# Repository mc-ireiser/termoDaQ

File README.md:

# termoDaQ

termoDaQ is a development board based on the [Arduino](https://www.arduino.cc/) architecture, uses an [ATmega328-P](http://ww1.microchip.com/downloads/en/DeviceDoc/Atmel-42735-8-bit-AVR-Microcontroller-ATmega328-328P_Summary.pdf) and an [ATtiny85](http://ww1.microchip.com/downloads/en/DeviceDoc/Atmel-2586-AVR-8-bit-Microcontroller-ATtiny25-ATtiny45-ATtiny85_Datasheet-Summary.pdf) for its operation.

This board was originally designed to help the work of oceanography students, serving as an instrument for the acquisition of physical variables (temperature, pressure) at surface level in bodies of fresh water, in order to detect changes that may affect the flora or fauna of ecosystems, automating the work of making measurements over time.

But it can serve many purposes since it has a connection for GPS receivers, pressure sensor, multiple temperature sensors (internal and external), two additional inputs for any analog sensor (such as rain, flow or UV) and SD card.

The function of the [ATtiny85](http://ww1.microchip.com/downloads/en/DeviceDoc/Atmel-2586-AVR-8-bit-Microcontroller-ATtiny25-ATtiny45-ATtiny85_Datasheet-Summary.pdf) is work as a timer to program the operation cycles of the equipment, reducing the energy consumption, which allows incrementing the operation time when the battery is used. To achieve this, activate and deactivate the sensors area.

The function of the [ATmega328-P](http://ww1.microchip.com/downloads/en/DeviceDoc/Atmel-42735-8-bit-AVR-Microcontroller-ATmega328-328P_Summary.pdf) is to control the sensors area, managing each of them to perform the measurement and data storage processes.

## Operation

The board is divided into three parts

1) Power supply.
2) Energy management.
3) Sensors area.

In particular, I'm responsible for developing the energy management and the sensors area.

For the energy management, is used the [ATtiny85](http://ww1.microchip.com/downloads/en/DeviceDoc/Atmel-2586-AVR-8-bit-Microcontroller-ATtiny25-ATtiny45-ATtiny85_Datasheet-Summary.pdf) microcontroller to carry out cycles that enable or disable the sensors, cutting off the power in periods where no measurements are needed.

As for the sensors area, its function is to perform the measurements and store the data. Only one cycle at a time, at the end one signal is sent to the energy management area to cut the power.

## Pinout

## Board specifications

All the source files are in this repository

- Board Size: 99.82 mm X 73.41 mm (X = 99.82, Y = 73.41)
- Number of layers: 2
- Number of drills: 311
- Number of vias: 47
- Number of signals: 146
- Minimum copper trace width: 0.41 mm
- Consumption: ~ 80mAh (currently under test)

### ATtiny85

|Name | Value |
| ---------- | ---------- |
|Operating Voltage Range (V) | 1.8 to 5.5 |
|Temperature Range (C) | -40 to 85 |
|CPU Speed (MIPS/DMIPS) | 20 |
|Pin Count | 8 |
|Program Memory Type | Flash |
|Program Memory Size (KB) | 8 |
|SRAM Bytes | 512 |
|Data EEPROM/HEF (bytes) | 512 |
|Digital Communication Peripherals | 1-SPI, 1-I2C |
|Capture/Compare/PWM Peripherals | 5PWM |
|Timers | 2 x 8-bit |
|Number of Comparators | 1 |

### ATmega328P

| Name | Value |
| ---------- | ---------- |
|Operating Supply Voltage | 1.8 V to 5.5 V |
|Temperature Range (C) | - 40 to 85 |
|Maximum Clock Frequency | 20 MHz |
|Pin count | 28 |
|Number of I/Os | 23 I/O |
|Program Memory Type | Flash |
|Program Memory Size | 32 kB |
|Data Bus Width | 8 bit |
|Data RAM Type | SRAM |
|Data RAM Size | 2 kB |
|Data ROM Type | EEPROM |
|Data ROM Size | 1 kB |
|Number of ADC Channels | 6 |
|ADC Resolution | 10 bit |
|Interface Type | I2C, SPI, USART |
|Number of Timers/Counters | 3 Timer |

## Translation

English translation using google translator.

If you wish, you can help me translate the readme file correctly.

## License

Creative Commons Attribution-ShareAlike 4.0 International Public License

Please go to the License section for more information. [Link](https://github.com/mc-ireiser/termoDaQ/tree/master/License)

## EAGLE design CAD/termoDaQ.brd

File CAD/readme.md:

# Description of files

- .brd source file with the design of the PCB
- .sch source file with the schematics of the board

These files are licensed under: Creative Commons Attribution-ShareAlike 4.0 International Public License

## Schematics

## Disclaimer

Last updated: October 05, 2018

(the "Service", files contained on this page)

Jesus Rodriguez assumes no responsibility for errors or omissions in the contents on the Service.

In no event shall Jesus Rodriguez be liable for any special, direct, indirect, consequential, or incidental damages or any damages whatsoever, whether in an action of contract, negligence or other tort, arising out of or in connection with the use of the Service or the contents of the Service. Jesus Rodriguez reserves the right to make additions, deletions, or modification to the contents on the Service at any time without prior notice.

This Disclaimer for Jesus Rodriguez is managed by TermsFeed Disclaimer Generator

Jesus Rodriguez does not warrant that the website is free of viruses or other harmful components.

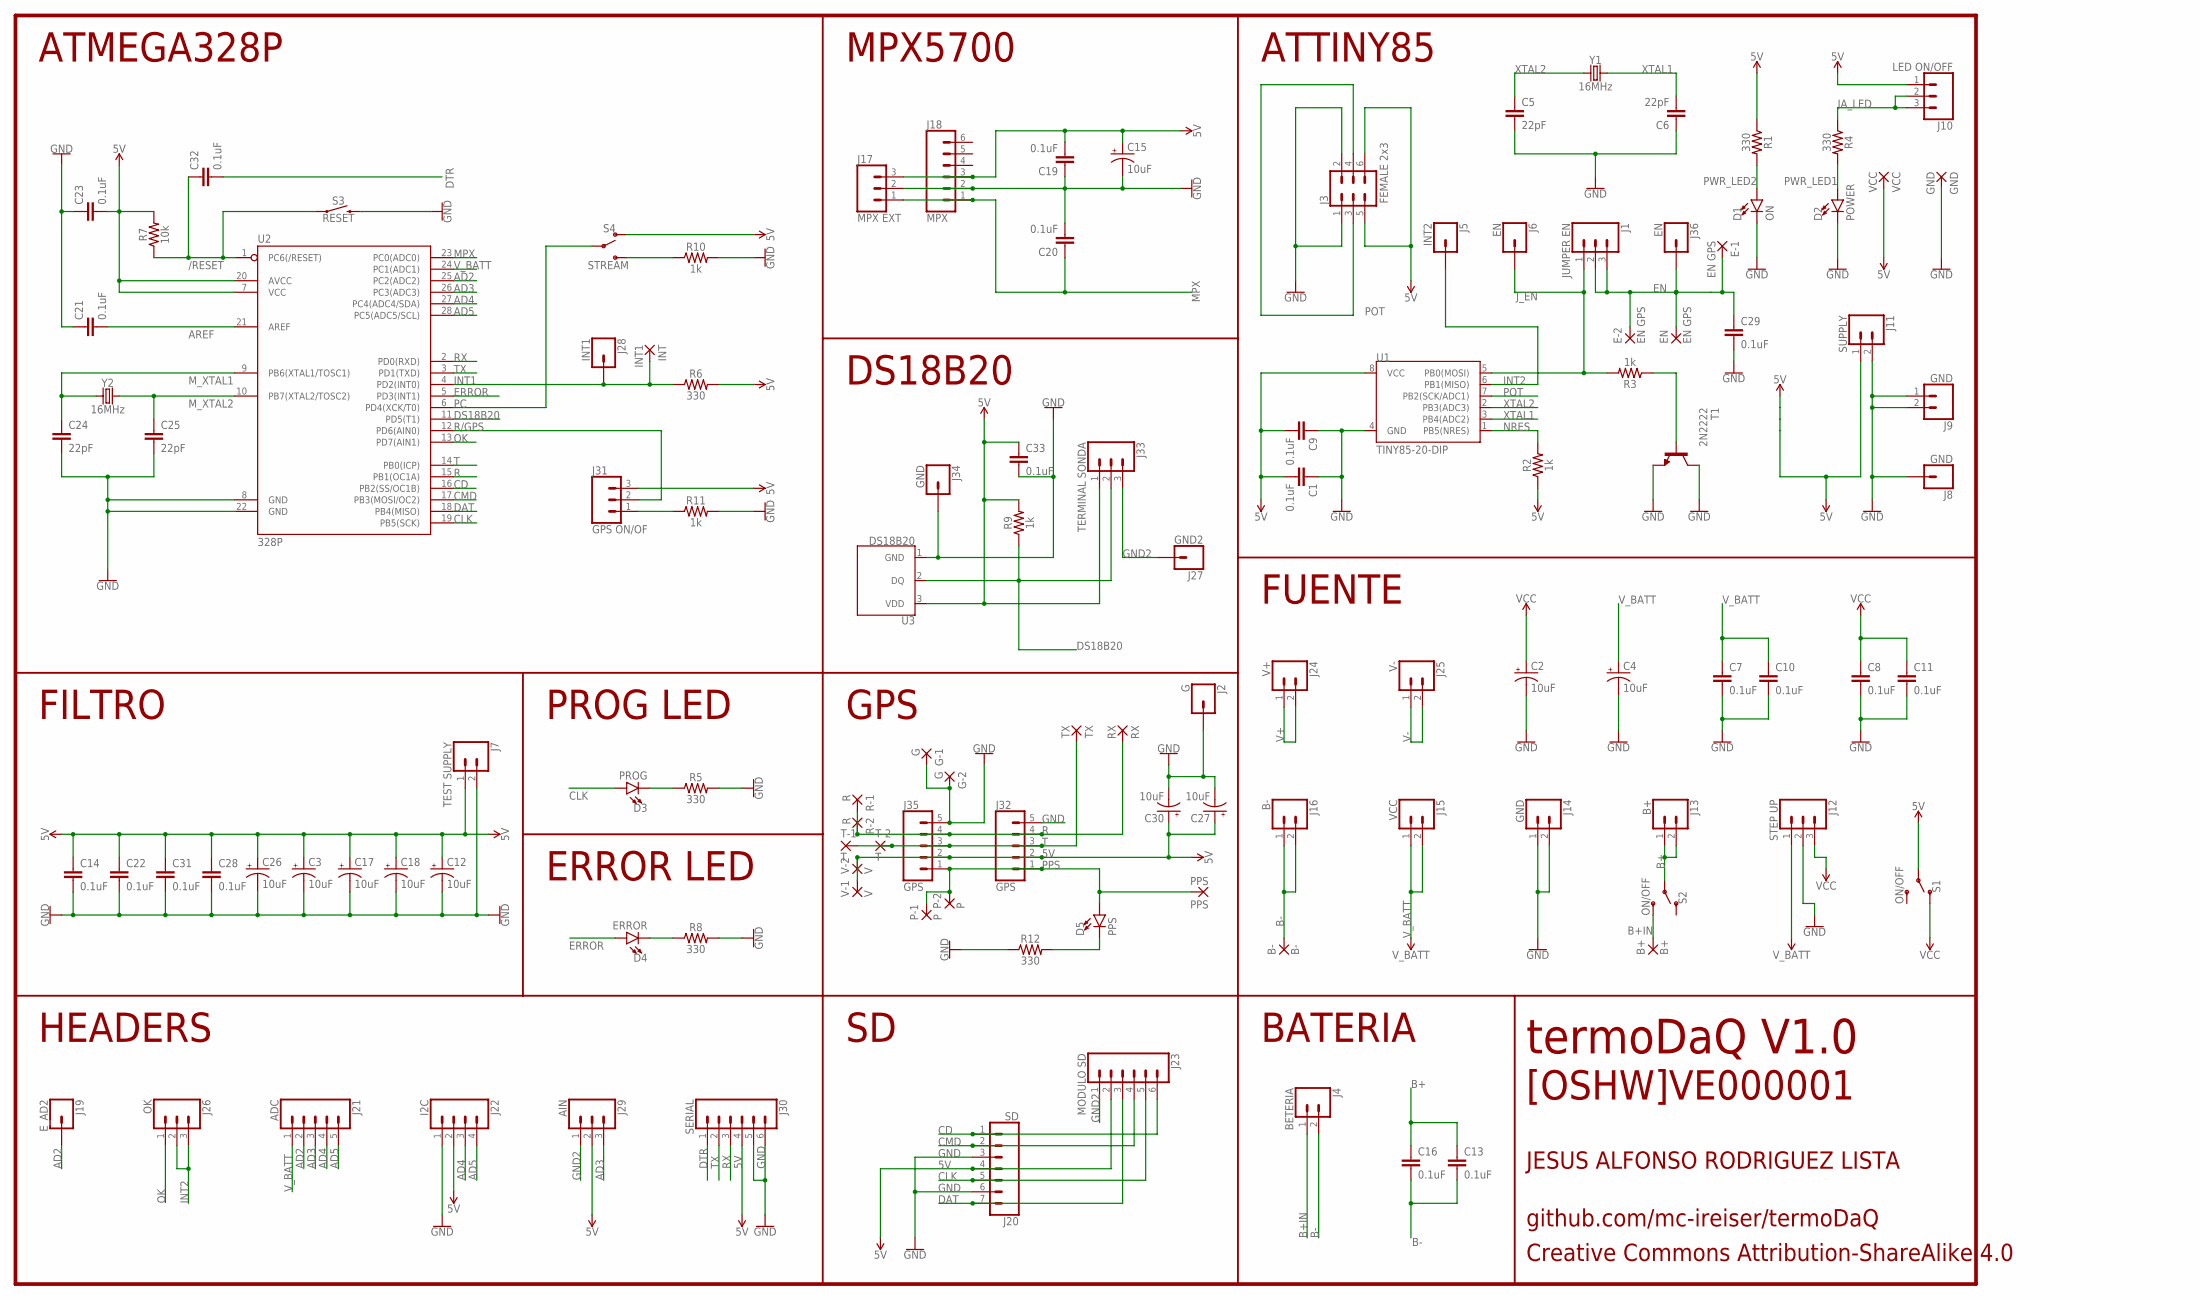
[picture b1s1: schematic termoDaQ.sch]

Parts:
B+: B+; SMD2,54-5,08
B-: B-; SMD2,54-5,08
C1, C7, C8, C9, C10, C11, C13, C14, C16, C19, C20, C21, C22, C23, C28, C29, C31, C32, C33: 0.1uF; CAP-PTH-SMALL-KIT
C2, C3, C4, C12, C15, C17, C18, C26, C27, C30: 10uF; CPOL-RADIAL-2.5MM-5MM
C5, C6, C24, C25: 22pF; CAP-PTH-2.54
D1: ON; LED_5MM
D2: POWER; LED_3MM
D3: PROG; LED_5MM
D4: ERROR; LED_5MM
D5: PPS; LED_5MM
E-1, E-2: EN GPS; SMD1,27-2,54
EN: EN GPS; SMD1,27-2,54
G-1, G-2: G; SMD1,27-2,54
GND: GND; SMD1,27-2,54
INT: INT1; SMD1,27-2,54
J1: JUMPER EN; 1X03
J2: G; 1X01
J3: FEMALE 2x3; 2X3
J4: BETERIA; 1X02
J5: INT2; 1X01
J6, J36: EN; 1X01
J7: TEST SUPPLY; 1X02
J8, J34: GND; 1X01
J9, J14: GND; 1X02
J10: LED ON/OFF; 1X03
J11: SUPPLY; 1X02
J12: STEP UP; 1X03
J13: B+; 1X02
J15: VCC; 1X02
J16: B-; 1X02
J17: MPX EXT; 1X03
J18: MPX; 1X06
J19: E_AD2; 1X01
J20: SD; 1X07
J21: ADC; 1X05
J22: I2C; 1X04
J23: MODULO SD; MOLEX-1X6
J24: V+; 1X02
J25: V-; 1X02
J26: OK; 1X03
J27: GND2; 1X01
J28: INT1; 1X01
J29: AIN; 1X03
J30: SERIAL; 1X06
J31: GPS ON/OF; 1X03
J32, J35: GPS; 1X05
J33: TERMINAL SONDA; SCREWTERMINAL-5MM-3
P-1, P-2: P; SMD1,27-2,54
PPS: PPS; SMD1,27-2,54
R1, R4, R5, R6, R8, R12: 330; AXIAL-0.3
R2, R3, R9, R10, R11: 1k; AXIAL-0.3
R7: 10k; AXIAL-0.3
R-1, R-2: R; SMD1,27-2,54
RX: RX; SMD1,27-2,54
S1, S2: ON/OFF; SWITCH_SPDT_PTH_11.6X4.0MM
S3: RESET; TACTILE_SWITCH_PTH_6.0MM
S4: STREAM; SWITCH_SPDT_PTH_11.6X4.0MM
T1: 2N2222; TO92-EBC-OVAL
T-1, T-2: T; SMD1,27-2,54
TX: TX; SMD1,27-2,54
U1: TINY85-20-DIP; DIP08_MCU
U2: 328P; DIP28
U3: DS18B20; TO-92-AMMO
V-1, V-2: V; SMD1,27-2,54
VCC: VCC; SMD1,27-2,54
Y1, Y2: 16MHz; HC49US

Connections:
5V: C1.2, C3.1 (+), C9.2, C12.1 (+), C14.1, C15.1 (+), C17.1 (+), C18.1 (+), C19.2, C22.1, C23.2, C26.1 (+), C27.1 (+), C28.1, C30.1 (+), C31.1, C33.1, J3.5, J3.6, J7.1, J10.1, J11.1, J17.3, J18.3, J20.4, J22.2, J23.2, J29.2, J30.4, J31.3, J32.2, J33.1, J35.2, R1.P$1 (1), R2.P$1 (1), R6.P$2 (2), R7.P$2 (2), R9.P$2 (2), S1.2, S4.1 (O), U1.8 (VCC), U2.7 (VCC), U2.20 (AVCC), U3.3 (VDD), V-1.1, V-2.1, VCC.1
/RESET: C32.1, R7.P$1 (1), S3.1, U2.1 (PC6(/RESET))
AD2: J19.1, J21.2, U2.25 (PC2(ADC2))
AD3: J21.3, J29.3, U2.26 (PC3(ADC3))
AD4: J21.4, J22.3, U2.27 (PC4(ADC4/SDA))
AD5: J21.5, J22.4, U2.28 (PC5(ADC5/SCL))
AREF: C21.2, U2.21 (AREF)
B+: C13.1, C16.1, J13.1, J13.2, S2.2
B+IN: B+.1, J4.1, S2.3 (S)
B-: B-.1, C13.2, C16.2, J4.2, J16.1, J16.2
CD: J20.1, J23.6, U2.16 (PB2(SS/OC1B))
CLK: D3.A, J20.5, J23.5, U2.19 (PB5(SCK))
CMD: J20.2, J23.4, U2.17 (PB3(MOSI/OC2))
DAT: J20.7, J23.3, U2.18 (PB4(MISO))
DS18B20: J33.2, R9.P$1 (1), U2.11 (PD5(T1)), U3.2 (DQ)
DTR: C32.2, J30.1
EN: C29.1, E-1.1, E-2.1, EN.1, J1.2, J1.3, J36.1
ERROR: D4.A, U2.5 (PD3(INT1))
GND: C1.1, C2.2 (-), C3.2 (-), C4.2 (-), C5.2, C6.1, C7.2, C8.2, C9.1, C10.2, C11.2, C12.2 (-), C14.2, C15.2 (-), C17.2 (-), C18.2 (-), C19.1, C20.2, C21.1, C22.2, C23.1, C24.2, C25.2, C26.2 (-), C27.2 (-), C28.2, C29.2, C30.2 (-), C31.2, C33.2, D1.K (C), D2.K (C), G-1.1, G-2.1, GND.1, J2.1, J3.1, J3.2, J7.2, J8.1, J9.1, J9.2, J11.2, J12.2, J14.1, J14.2, J17.2, J18.2, J20.3, J20.6, J22.1, J30.5, J30.6, J32.5, J34.1, J35.5, R5.P$2 (2), R8.P$2 (2), R10.P$2 (2), R11.P$2 (2), R12.P$1 (1), S3.3 (2), T1.C, T1.E, U1.4 (GND), U2.8 (GND), U2.22 (GND), U3.1 (GND)
GND2: J23.1, J27.1, J29.1, J33.3
INT1: INT.1, J28.1, R6.P$1 (1), U2.4 (PD2(INT0))
INT2: J5.1, J26.2, J26.3, U1.6 (PB1(MISO))
JA_LED: J10.2, J10.3, R4.P$1 (1)
J_EN: J1.1, J6.1, R3.P$2 (2), U1.5 (PB0(MOSI))
MPX: C20.1, J17.1, J18.1, U2.23 (PC0(ADC0))
M_XTAL1: C24.1, U2.9 (PB6(XTAL1/TOSC1)), Y2.1
M_XTAL2: C25.1, U2.10 (PB7(XTAL2/TOSC2)), Y2.2
unnamed: D3.K (C), R5.P$1 (1)
unnamed: D5.K (C), R12.P$2 (2)
unnamed: D4.K (C), R8.P$1 (1)
unnamed: J31.1, R11.P$1 (1)
unnamed: R10.P$1 (1), S4.3 (S)
unnamed: R3.P$1 (1), T1.B
NRES: R2.P$2 (2), U1.1 (PB5(NRES))
OK: J26.1, U2.13 (PD7(AIN1))
PC: S4.2, U2.6 (PD4(XCK/T0))
POT: J3.3, J3.4, U1.7 (PB2(SCK/ADC1))
PPS: D5.A, J32.1, J35.1, P-1.1, P-2.1, PPS.1
PWR_LED1: D2.A, R4.P$2 (2)
PWR_LED2: D1.A, R1.P$2 (2)
R: J32.4, J35.4, R-1.1, R-2.1, RX.1, U2.15 (PB1(OC1A))
R/GPS: J31.2, U2.12 (PD6(AIN0))
RX: J30.3, U2.2 (PD0(RXD))
T: J32.3, J35.3, T-1.1, T-2.1, TX.1, U2.14 (PB0(ICP))
TX: J30.2, U2.3 (PD1(TXD))
V+: J24.1, J24.2
V-: J25.1, J25.2
VCC: C2.1 (+), C8.1, C11.1, J12.3, S1.1 (O)
V_BATT: C4.1 (+), C7.1, C10.1, J12.1, J15.1, J15.2, J21.1, U2.24 (PC1(ADC1))
XTAL1: C6.2, U1.3 (PB4(ADC2)), Y1.2
XTAL2: C5.1, U1.2 (PB3(ADC3)), Y1.1

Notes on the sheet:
FUENTE
ATTINY85
ATMEGA328P
HEADERS
JESUS ALFONSO RODRIGUEZ LISTA
GPS
DS18B20
MPX5700
PROG LED
FILTRO
ERROR LED
BATERIA
[OSHW]VE000001
github.com/mc-ireiser/termoDaQ
Creative Commons Attribution-ShareAlike 4.0
termoDaQ V1.0

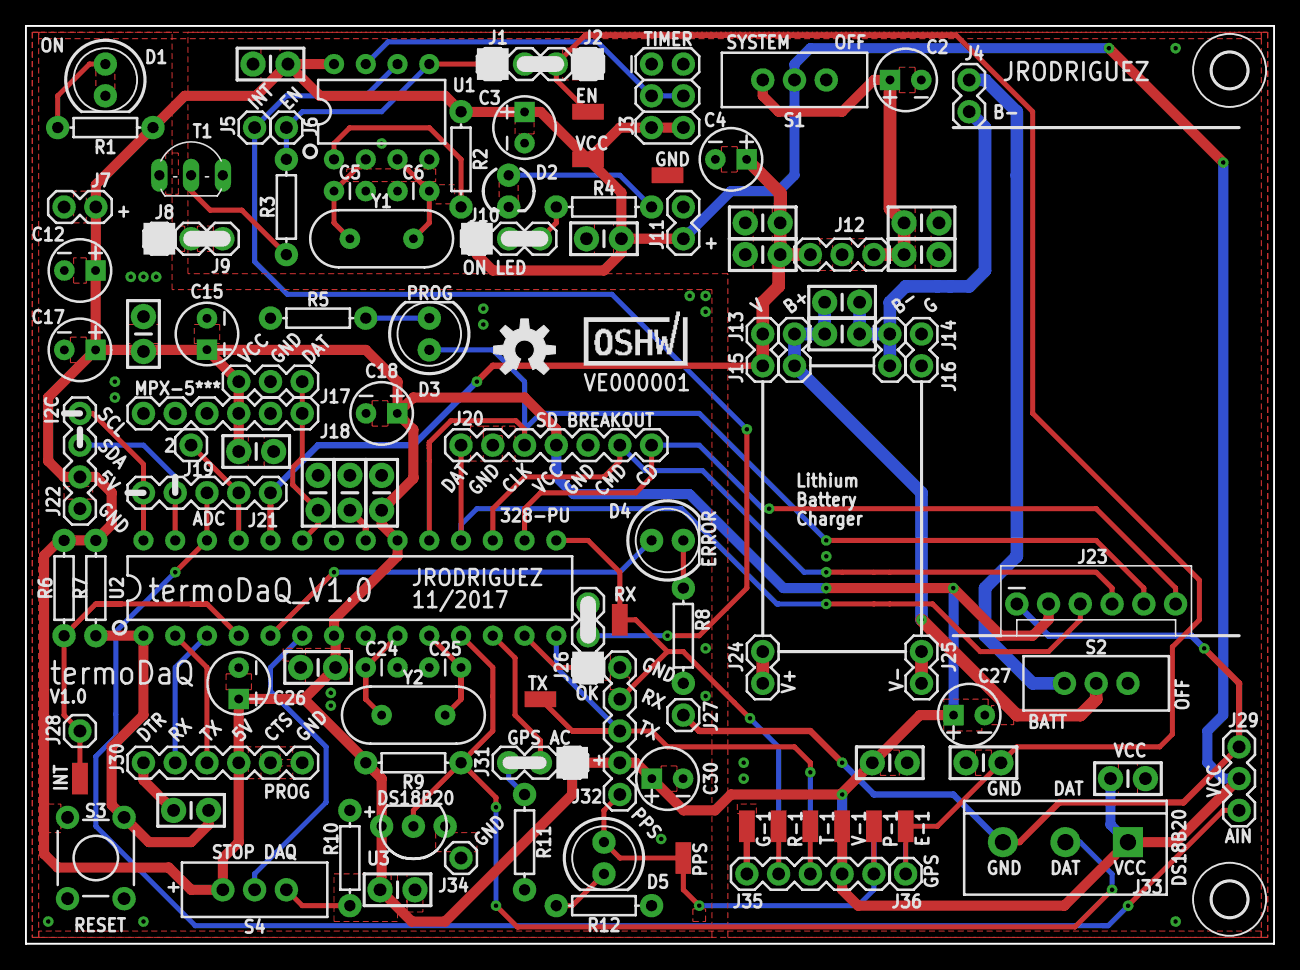
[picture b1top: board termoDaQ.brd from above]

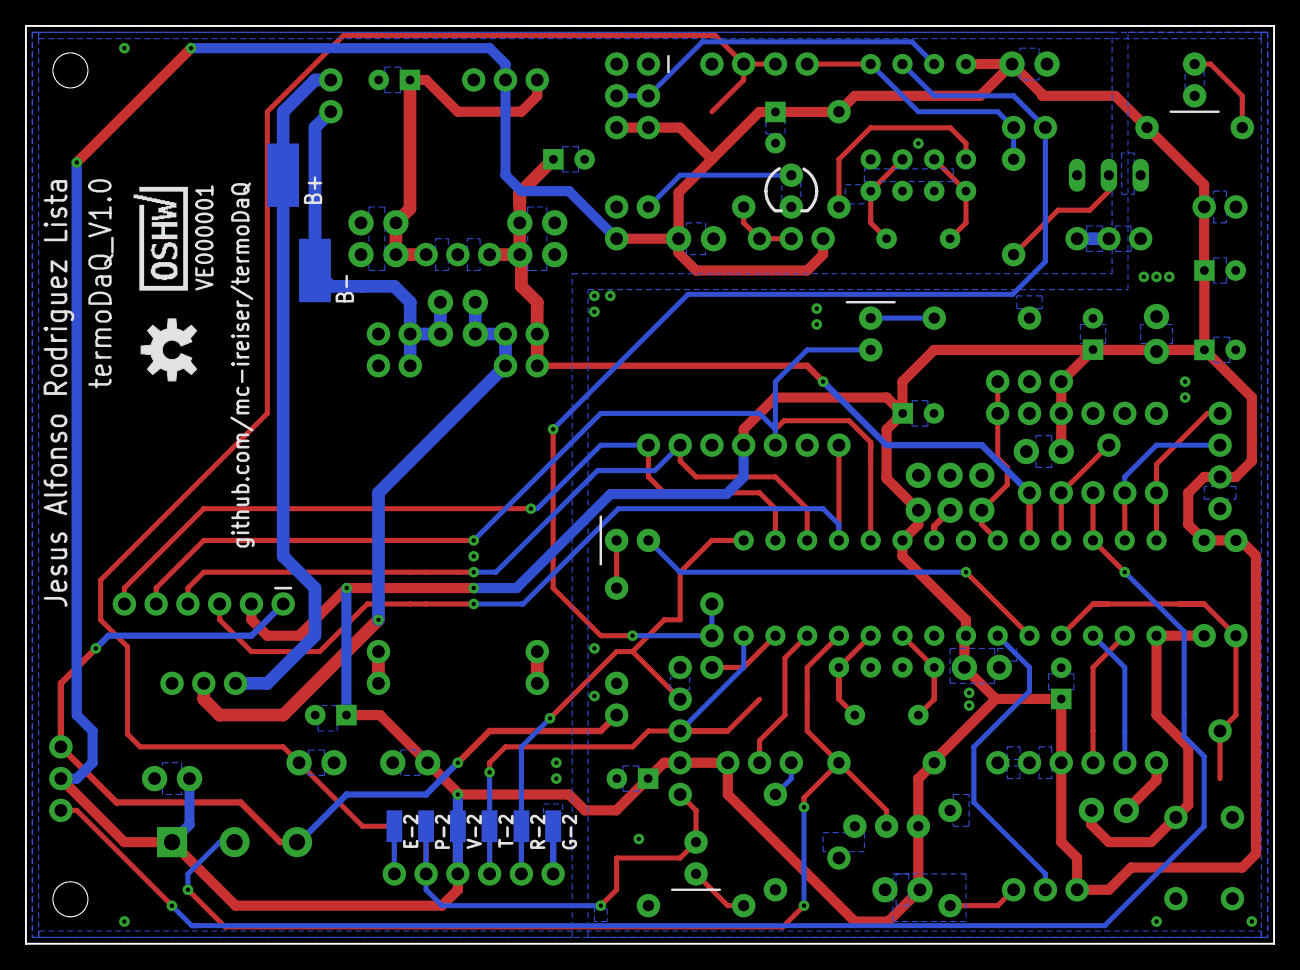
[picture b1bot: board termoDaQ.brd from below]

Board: 2 copper layers, 99.8 x 73.4 mm, 123 parts (10 on the bottom side), 51 nets.

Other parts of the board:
U$1, U$100: OSHW-LOGO-M
U$2, U$101: CERT-SMALL-SILK
U$3, U$4: 2,8

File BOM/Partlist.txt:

Partlist

Exported from termoDaQ.brd

EAGLE Version 9.1.3 Copyright (c) 1988-2018 Autodesk, Inc.

Assembly variant: 

Part     Value          Package                    Library                     Position (inch)       Orientation

C1       0.1uF          CAP-PTH-SMALL-KIT          SparkFun-Capacitors         (0.8 2.8)             R0
C2       10uF           CPOL-RADIAL-2.5MM-5MM      SparkFun-Capacitors         (2.8 2.75)            R180
C3       10uF           CPOL-RADIAL-2.5MM-5MM      SparkFun-Capacitors         (1.6 2.6)             R90
C4       10uF           CPOL-RADIAL-2.5MM-5MM      SparkFun-Capacitors         (2.25 2.5)            R0
C5       22pF           CAP-PTH-2.54               SparkFun-Capacitors         (1.05 2.4)            R0
C6       22pF           CAP-PTH-2.54               SparkFun-Capacitors         (1.25 2.4)            R0
C7       0.1uF          CAP-PTH-SMALL-KIT          SparkFun-Capacitors         (2.35 2.3)            R180
C8       0.1uF          CAP-PTH-SMALL-KIT          SparkFun-Capacitors         (2.85 2.3)            R0
C9       0.1uF          CAP-PTH-SMALL-KIT          SparkFun-Capacitors         (1.85 2.25)           R0
C10      0.1uF          CAP-PTH-SMALL-KIT          SparkFun-Capacitors         (2.35 2.2)            R180
C11      0.1uF          CAP-PTH-SMALL-KIT          SparkFun-Capacitors         (2.85 2.2)            R0
C12      10uF           CPOL-RADIAL-2.5MM-5MM      SparkFun-Capacitors         (0.2 2.15)            R0
C13      0.1uF          CAP-PTH-SMALL-KIT          SparkFun-Capacitors         (2.6 2.05)            R0
C14      0.1uF          CAP-PTH-SMALL-KIT          SparkFun-Capacitors         (0.4 1.95)            R90
C15      10uF           CPOL-RADIAL-2.5MM-5MM      SparkFun-Capacitors         (0.6 1.95)            R270
C16      0.1uF          CAP-PTH-SMALL-KIT          SparkFun-Capacitors         (2.6 1.95)            R0
C17      10uF           CPOL-RADIAL-2.5MM-5MM      SparkFun-Capacitors         (0.2 1.9)             R0
C18      10uF           CPOL-RADIAL-2.5MM-5MM      SparkFun-Capacitors         (1.15 1.7)            R0
C19      0.1uF          CAP-PTH-SMALL-KIT          SparkFun-Capacitors         (0.755 1.58)          R180
C20      0.1uF          CAP-PTH-SMALL-KIT          SparkFun-Capacitors         (0.95 1.45)           R90
C21      0.1uF          CAP-PTH-SMALL-KIT          SparkFun-Capacitors         (1.05 1.45)           R270
C22      0.1uF          CAP-PTH-SMALL-KIT          SparkFun-Capacitors         (1.15 1.45)           R90
C23      0.1uF          CAP-PTH-SMALL-KIT          SparkFun-Capacitors         (0.95 0.9)            R0
C24      22pF           CAP-PTH-2.54               SparkFun-Capacitors         (1.15 0.9)            R0
C25      22pF           CAP-PTH-2.54               SparkFun-Capacitors         (1.35 0.9)            R180
C26      10uF           CPOL-RADIAL-2.5MM-5MM      SparkFun-Capacitors         (0.7 0.85)            R270
C27      10uF           CPOL-RADIAL-2.5MM-5MM      SparkFun-Capacitors         (3 0.75)              R180
C28      0.1uF          CAP-PTH-SMALL-KIT          SparkFun-Capacitors         (2.75 0.6)            R0
C29      0.1uF          CAP-PTH-SMALL-KIT          SparkFun-Capacitors         (3.045 0.6)           R180
C30      10uF           CPOL-RADIAL-2.5MM-5MM      SparkFun-Capacitors         (2.05 0.55)           R180
C31      0.1uF          CAP-PTH-SMALL-KIT          SparkFun-Capacitors         (3.5 0.55)            R0
C32      0.1uF          CAP-PTH-SMALL-KIT          SparkFun-Capacitors         (0.55 0.45)           R180
C33      0.1uF          CAP-PTH-SMALL-KIT          SparkFun-Capacitors         (1.2 0.2)             R0
D1       ON             LED_5MM                    SparkFun-LED                (0.28 2.75)           R270
D2       POWER          LED_3MM                    SparkFun-LED                (1.55 2.4)            R270
D3       PROG           LED_5MM                    SparkFun-LED                (1.3 1.95)            R90
D4       ERROR          LED_5MM                    SparkFun-LED                (2.05 1.3)            R0
D5       PPS            LED_5MM                    SparkFun-LED                (1.85 0.3)            R270
J1       JUMPER EN      1X03                       SparkFun-Connectors         (1.5 2.8)             R0
J4       BETERIA        1X02                       SparkFun-Connectors         (3 2.75)              R270
J7       TEST SUPPLY    1X02                       SparkFun-Connectors         (0.25 2.35)           R180
J10      LED ON/OFF     1X03                       SparkFun-Connectors         (1.45 2.25)           R0
J11      SUPPLY         1X02                       SparkFun-Connectors         (2.1 2.25)            R90
J22      I2C            1X04                       SparkFun-Connectors         (0.2 1.4)             R90
J26      OK             1X03                       SparkFun-Connectors         (1.8 0.9)             R90
J30      SERIAL         1X06                       SparkFun-Connectors         (0.4 0.6)             R0
J31      GPS ON/OF      1X03                       SparkFun-Connectors         (1.55 0.6)            R0
J33      TERMINAL SONDA SCREWTERMINAL-5MM-3        SparkFun-Connectors         (3.5 0.35)            R180
R1       330            AXIAL-0.3                  SparkFun-Resistors          (0.28 2.6)            R180
R2       1k             AXIAL-0.3                  SparkFun-Resistors          (1.4 2.5)             R270
R3       1k             AXIAL-0.3                  SparkFun-Resistors          (0.85 2.35)           R90
R4       330            AXIAL-0.3                  SparkFun-Resistors          (1.85 2.35)           R0
R5       330            AXIAL-0.3                  SparkFun-Resistors          (0.95 2)              R180
R6       330            AXIAL-0.3                  SparkFun-Resistors          (0.15 1.15)           R90
R7       10k            AXIAL-0.3                  SparkFun-Resistors          (0.25 1.15)           R90
R8       330            AXIAL-0.3                  SparkFun-Resistors          (2.1 1)               R270
R9       1k             AXIAL-0.3                  SparkFun-Resistors          (1.25 0.6)            R180
R10      1k             AXIAL-0.3                  SparkFun-Resistors          (1.05 0.3)            R90
R11      1k             AXIAL-0.3                  SparkFun-Resistors          (1.6 0.35)            R270
R12      330            AXIAL-0.3                  SparkFun-Resistors          (1.85 0.15)           R180
S1       ON/OFF         SWITCH_SPDT_PTH_11.6X4.0MM SparkFun-Switches           (2.45 2.75)           R90
S2       ON/OFF         SWITCH_SPDT_PTH_11.6X4.0MM SparkFun-Switches           (3.4 0.85)            R270
S3       RESET          TACTILE_SWITCH_PTH_6.0MM   SparkFun-Switches           (0.25 0.3)            R270
S4       STREAM         SWITCH_SPDT_PTH_11.6X4.0MM SparkFun-Switches           (0.75 0.2)            R90
T1       2N2222         TO92-EBC-OVAL              adafruit                    (0.55 2.5)            R0
TX       TX             SMD1,27-2,54               wirepad                     (1.65 0.8)            R270
U1       TINY85-20-DIP  DIP08_MCU                  SparkFun-Retired            (1.15 2.65)           R0
U2       328P           DIP28                      SparkFun-IC-Microcontroller (1.05 1.15)           R0
U3       DS18B20        TO-92-AMMO                 SparkFun-Sensors            (1.25 0.4)            R180
Y1       16MHz          HC49US                     SparkFun-Clocks             (1.15 2.25)           R0
Y2       16MHz          HC49US                     SparkFun-Clocks             (1.25 0.75)           R0

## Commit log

2017-11-21 2D Render images files
2017-11-21 3D Render images files
2017-11-21 Bom and Partlist
2017-11-21 Source files .brd and .sch from Eagle 8.4
2017-11-21 Gerbers files for FAB
2017-11-21 images of Overall an Copper
2017-11-21 Libraries Adafruit and SparkFun - source link and .zip
2017-11-21 Licence info
2017-11-21 PDF files of board and Schematics
2017-11-21 STL model, only for demo!
2017-11-21 Firmware Attention
2017-11-21 Proroboard Assembly full test
2017-11-21 License repo link
2017-11-21 Link to test assembly img
2017-11-21 Link of license files
2017-11-21 include images
2017-11-21 License logo
2017-11-21 License update
2017-11-21 update title
2017-11-21 Set theme jekyll-theme-cayman
2017-11-21 aclaration
2017-11-21 docs folder add
2017-11-22 Create CNAME
2017-11-23 Update CNAME
2017-11-23 Example mockup
2017-11-23 Update mockup
2017-11-23 Updated mockup
2017-11-23 Delete
2017-11-23 Creative commons img
2017-11-23 Set theme jekyll-theme-leap-day
2017-11-23 Readme for preview
2017-11-23 Correction
2017-11-23 Description of files
2017-11-23 Pinout
2017-11-23 No copper preview
2017-11-24 updated with pinout
2017-11-25 Readme update
2017-11-25 Source files update
2017-11-25 New STL model
2017-11-25 Partlist update
2017-11-25 Expand Pinout IMG
2017-11-25 Re-Upload images files
2017-11-25 Re-Upload PDF files
2017-11-25 BOM on ods format
2017-11-25 Repair header
2017-11-25 Add 2D render
2017-11-25 Add Pending
2017-11-26 Fix 2D Render header
2017-11-26 Important update, start the manufacturing process in PCB
2017-11-26 add .
2018-01-19 Gerbers update
2018-01-19 Delay
2018-01-19 Info update!
2018-01-19 Photographs of the assembled board
2018-01-19 PCB assembled
2018-01-19 Update from main README
2018-01-19 img order
2018-01-20 STL model
2018-09-07 README
2018-09-07 Pendings list
2018-09-07 Old Update
2018-10-05 New 2D render
2018-10-05 Update, part list
2018-10-05 Source files, Update
2018-10-05 Prev img
2018-10-05 Updated, Gerbers files
2018-10-05 Updated, PDF schematics
2018-10-05 Update, Readme
2018-10-05 Link to new OSHWA page
2018-10-05 Disclaimer
2018-10-05 Update, Img
2018-10-05 Update, photographs
2018-10-05 3D render "old"
    Update required
2018-10-05 Fix format img
2018-10-05 Header img
2018-10-05 New schema
2018-10-05 Update, info
2018-10-05 Update, docs Readme
2018-10-05 Update, Disclaimer
2018-10-05 Update, Intro
2018-10-05 Update, Board specifications
2018-10-05 Fix table error
2018-10-05 Update, Names
2018-10-05 Update, Pinout
2018-10-05 Goals Complete
2018-10-06 Code of conduct

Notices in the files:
CAD/termoDaQ.brd:
Is licensed under: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
parts and their libraries:
SparkFun-IC-Microcontroller: Licensing: Creative Commons ShareAlike 4.0 International - https://creativecommons.org/licenses/by-sa/4.0
